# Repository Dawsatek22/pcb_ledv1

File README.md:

# pcb_ledv1
my first attempt to make a pcb

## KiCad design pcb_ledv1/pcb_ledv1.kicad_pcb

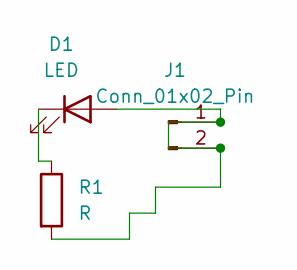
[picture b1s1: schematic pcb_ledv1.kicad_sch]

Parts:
D1: LED; LED_D3.0mm
J1: Conn_01x02_Pin; PinHeader_1x02_P2.54mm_Vertical
R1: R; R_0201_0603Metric

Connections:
unnamed: D1.2 (A), J1.1, J1.2, R1.2
unnamed: D1.1 (K), R1.1

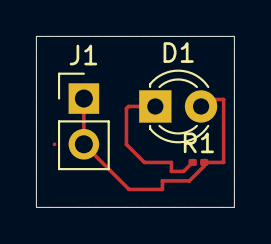
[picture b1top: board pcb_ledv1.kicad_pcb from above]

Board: 2 copper layers, 11.0 x 9.5 mm, 3 parts (0 on the bottom side), 2 nets.
